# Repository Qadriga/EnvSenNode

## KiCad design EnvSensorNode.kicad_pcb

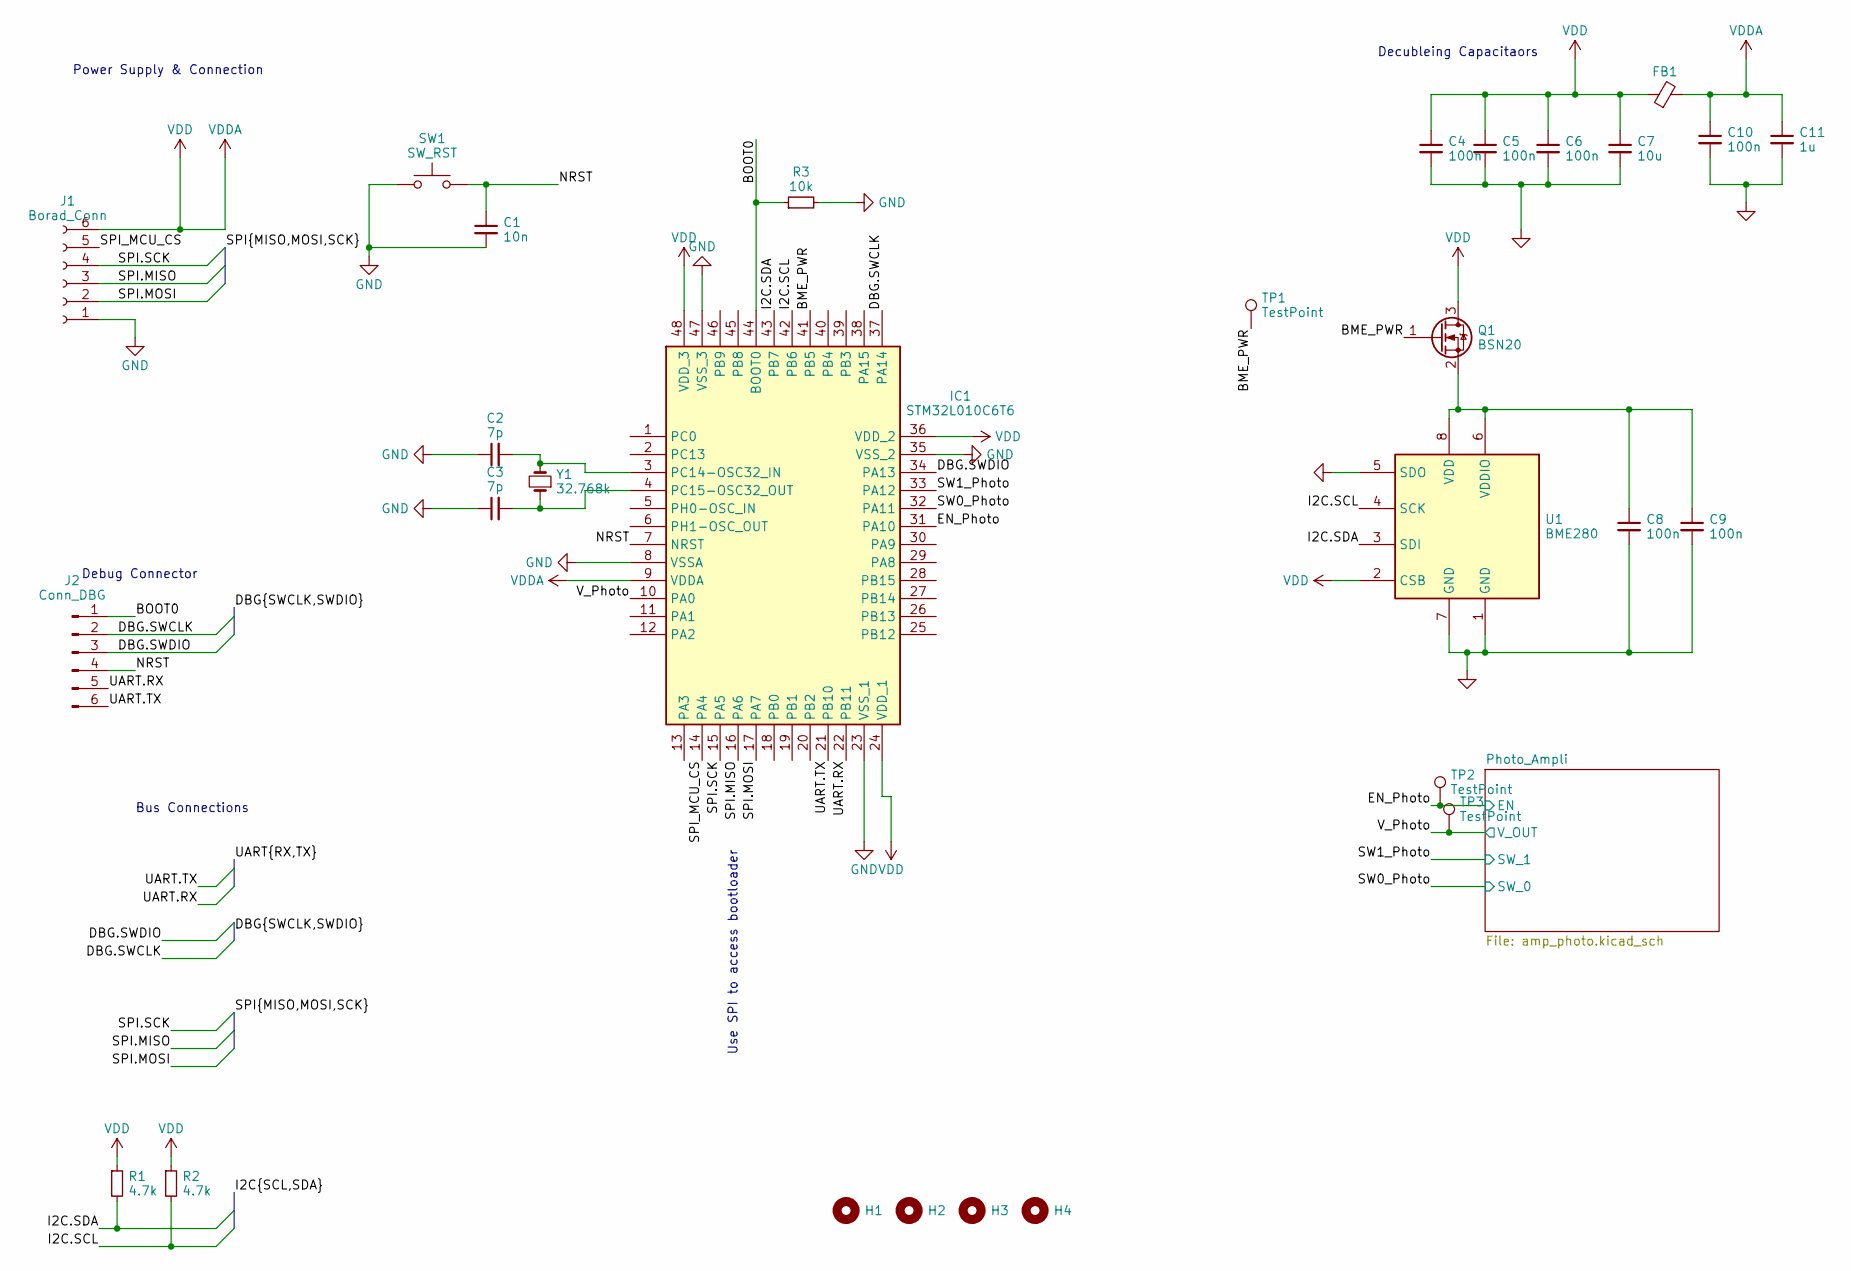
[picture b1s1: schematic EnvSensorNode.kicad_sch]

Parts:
C1: 10n; C_0402_1005Metric_Pad0.74x0.62mm_HandSolder
C2, C3: 7p; C_0402_1005Metric_Pad0.74x0.62mm_HandSolder
C4, C5, C6, C8, C9, C10: 100n; C_0402_1005Metric_Pad0.74x0.62mm_HandSolder
C7: 10u; C_0402_1005Metric_Pad0.74x0.62mm_HandSolder
C11: 1u; C_0402_1005Metric_Pad0.74x0.62mm_HandSolder
FB1: FerriteBead_Small; L_0402_1005Metric_Pad0.77x0.64mm_HandSolder
H1, H2, H3, H4: MountingHole; MountingHole_2.1mm
IC1: STM32L010C6T6; QFP50P900X900X160-48N; Mouser Part Number 511-STM32L010C6T6
J1: Borad_Conn; PinHeader_1x06_P1.27mm_Vertical
J2: Conn_DBG; PinHeader_1x06_P1.27mm_Vertical
Q1: BSN20; SOT-23; Manufacturer_Part_Number BSN20-7; Mouser Part Number 621-BSN20-7
R1, R2: 4.7k; R_0201_0603Metric_Pad0.64x0.40mm_HandSolder
R3: 10k; R_0201_0603Metric_Pad0.64x0.40mm_HandSolder
SW1: SW_RST; SW_SPST_B3U-1000P
TP1, TP2, TP3: TestPoint; TestPoint_Pad_D1.5mm
U1: BME280; Bosch_LGA-8_2.5x2.5mm_P0.65mm_ClockwisePinNumbering; Manufacturer_Part_Number BME280; Mouser Part Number 262-BME280
Y1: 32.768k; Crystal_SMD_3215-2Pin_3.2x1.5mm; Manufacturer_Part_Number ECS-.327-7-34QCS-TR9; Mouser Part Number 520-ECS-327734QCSTR9

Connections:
/BME_PWR: IC1.41 (PB5), Q1.1 (G), TP1.1
/BOOT0: IC1.44 (BOOT0), J2.1, R3.1
/DBG.SWCLK: IC1.37 (PA14), J2.2
/DBG.SWDIO: IC1.34 (PA13), J2.3
/EN_Photo: IC1.31 (PA10), TP2.1; also elsewhere on the board
/I2C.SCL: IC1.42 (PB6), R2.2, U1.4 (SCK)
/I2C.SDA: IC1.43 (PB7), R1.2, U1.3 (SDI)
/NRST: C1.1, IC1.7 (NRST), J2.4, SW1.2
/SPI.MISO: IC1.16 (PA6), J1.3
/SPI.MOSI: IC1.17 (PA7), J1.2
/SPI.SCK: IC1.15 (PA5), J1.4
/SPI_MCU_CS: IC1.14 (PA4), J1.5
/SW0_Photo: IC1.32 (PA11); also elsewhere on the board
/SW1_Photo: IC1.33 (PA12); also elsewhere on the board
/UART.RX: IC1.22 (PB11), J2.5
/UART.TX: IC1.21 (PB10), J2.6
/V_Photo: IC1.10 (PA0), TP3.1; also elsewhere on the board
GND: C1.2, C2.1, C3.1, C4.2, C5.2, C6.2, C7.2, C8.2, C9.2, C10.2, C11.2, IC1.8 (VSSA), IC1.23 (VSS_1), IC1.35 (VSS_2), IC1.47 (VSS_3), J1.1, R3.2, SW1.1, U1.1 (GND), U1.5 (SDO), U1.7 (GND); also elsewhere on the board
unnamed: C2.2, IC1.3 (PC14-OSC32_IN), Y1.2
unnamed: C3.2, IC1.4 (PC15-OSC32_OUT), Y1.1
unnamed: C8.1, C9.1, Q1.2 (S), U1.6 (VDDIO), U1.8 (VDD)
VDD: C4.1, C5.1, C6.1, C7.1, C10.1, C11.1, FB1.1, FB1.2, IC1.9 (VDDA), IC1.24 (VDD_1), IC1.36 (VDD_2), IC1.48 (VDD_3), J1.6, Q1.3 (D), R1.1, R2.1, U1.2 (CSB); also elsewhere on the board

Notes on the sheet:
Debug Connector
Power Supply & Connection
Decubleing Capacitaors
Bus Connections
Use SPI to access bootloader

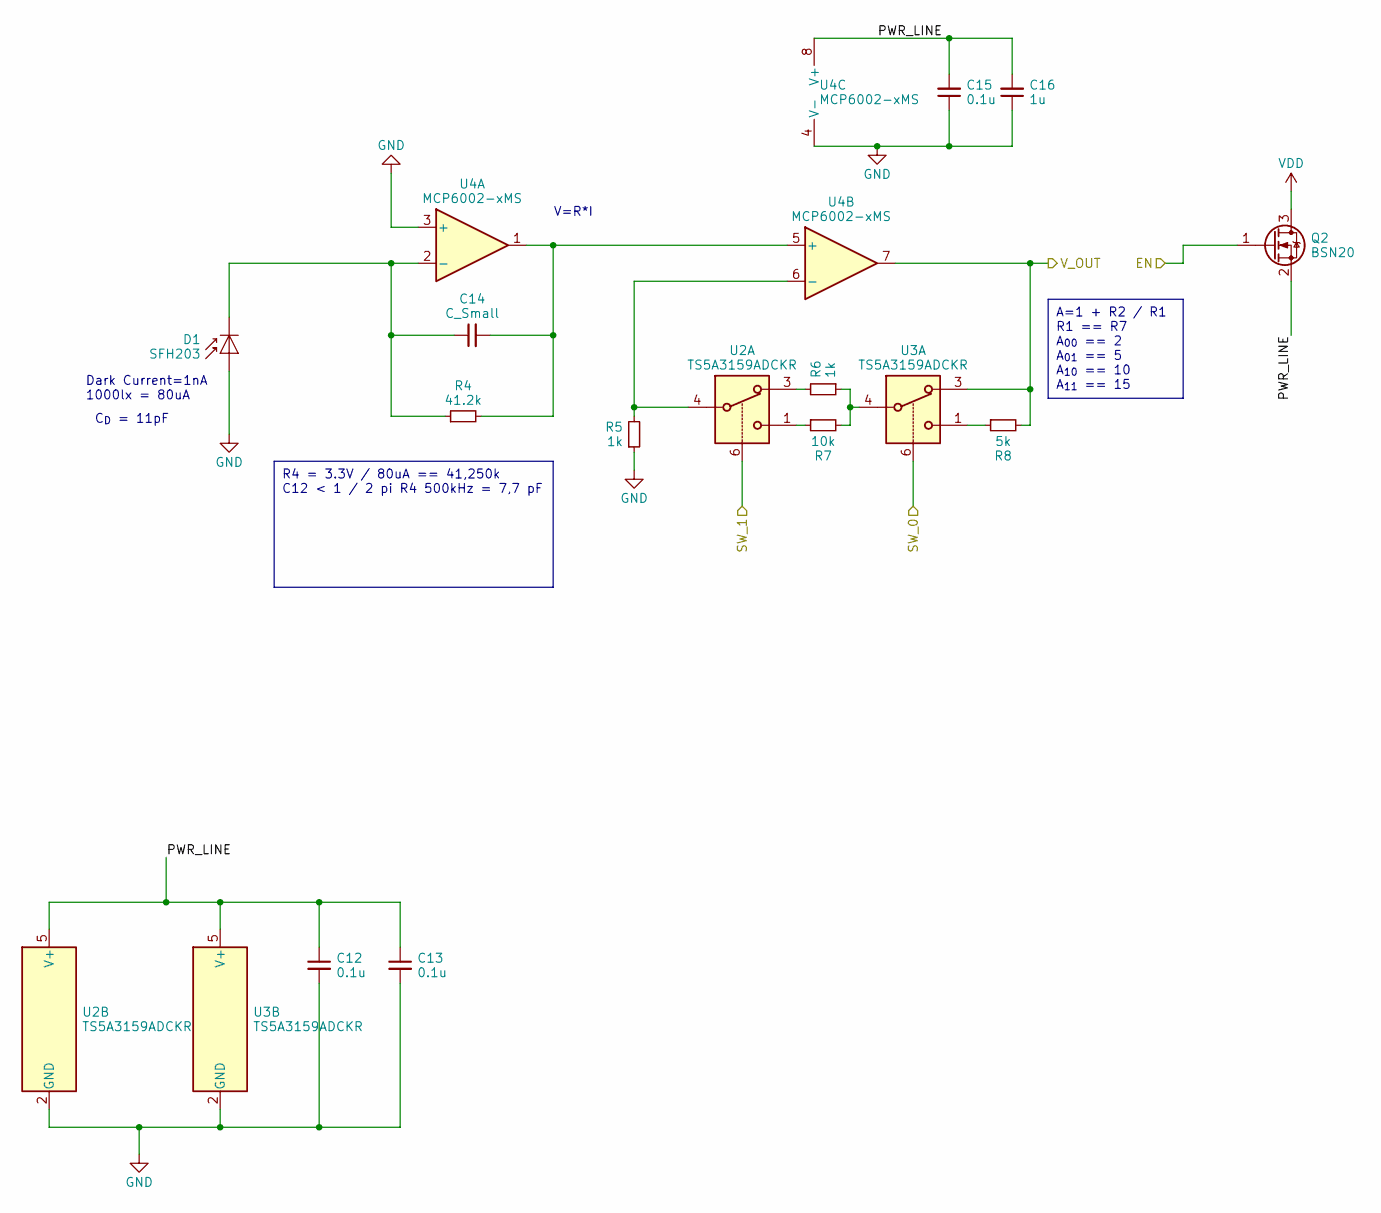
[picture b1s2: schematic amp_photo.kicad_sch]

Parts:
C12, C13, C15: 0.1u; C_0402_1005Metric_Pad0.74x0.62mm_HandSolder
C14: C_Small; C_0402_1005Metric_Pad0.74x0.62mm_HandSolder
C16: 1u; C_0402_1005Metric_Pad0.74x0.62mm_HandSolder
D1: SFH203; LED_D5.0mm_IRGrey; Manufacturer_Part_Number SFH 203; Mouser Part Number 720-SFH203
Q2: BSN20; SOT-23; Manufacturer_Part_Number BSN20-7; Mouser Part Number 621-BSN20-7
R4: 41.2k; R_0201_0603Metric_Pad0.64x0.40mm_HandSolder
R5, R6: 1k; R_0201_0603Metric_Pad0.64x0.40mm_HandSolder
R7: 10k; R_0201_0603Metric_Pad0.64x0.40mm_HandSolder
R8: 5k; R_0201_0603Metric_Pad0.64x0.40mm_HandSolder
U2, U3: TS5A3159ADCKR; SOT-363_SC-70-6; Manufacturer_Part_Number TS5A3159ADCKR; Mouser Part Number 595-TS5A3159ADCKR
U4: MCP6002-xMS; SOIC-8_3.9x4.9mm_P1.27mm; Manufacturer_Part_Number MCP6002-I/SN; Mouser Part Number MCP6002-I/SN

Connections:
/EN_Photo: Q2.1 (G); also elsewhere on the board
/Photo_Ampli/PWR_LINE: C12.1, C13.1, C15.2, C16.2, Q2.2 (S), U2.5 (V+), U3.5 (V+), U4.8 (V+)
/SW0_Photo: U3.6; also elsewhere on the board
/SW1_Photo: U2.6; also elsewhere on the board
/V_Photo: R8.2, U3.3, U4.7; also elsewhere on the board
GND: C12.2, C13.2, C15.1, C16.1, D1.2 (A), R5.1, U2.2 (GND), U3.2 (GND), U4.3 (+), U4.4 (V-); also elsewhere on the board
unnamed: C14.1, D1.1 (K), R4.1, U4.2 (-)
unnamed: R6.1, R7.2, U3.4
unnamed: R6.2, U2.3
unnamed: R7.1, U2.1
unnamed: R8.1, U3.1
unnamed: C14.2, R4.2, U4.1, U4.5 (+)
unnamed: R5.2, U2.4, U4.6 (-)
VDD: Q2.3 (D); also elsewhere on the board

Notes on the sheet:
A=1 + R2 / R1 R1 == R7 A_{00} == 2 A_{01} == 5 A_{10} == 10 A_{11} == 15
R4 = 3.3V / 80uA == 41,250k C12 < 1 / 2 pi R4 500kHz = 7,7 pF
C_{D} = 11pF
V=R*I
Dark Current=1nA 1000lx = 80uA

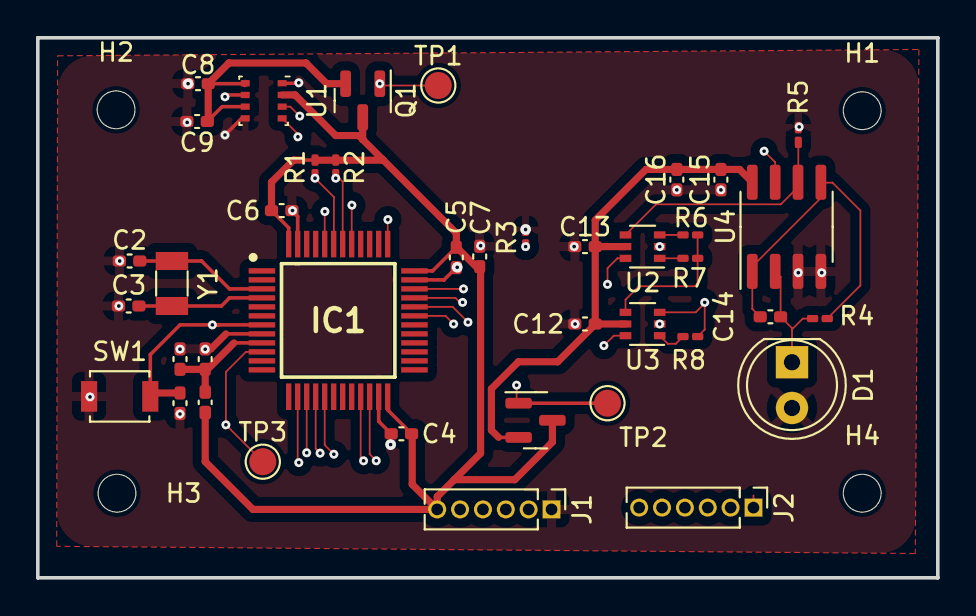
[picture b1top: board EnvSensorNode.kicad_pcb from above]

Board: 4 copper layers, 50.0 x 30.0 mm, 44 parts (0 on the bottom side), 30 nets.

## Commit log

2023-07-03 Make top gnd plane
